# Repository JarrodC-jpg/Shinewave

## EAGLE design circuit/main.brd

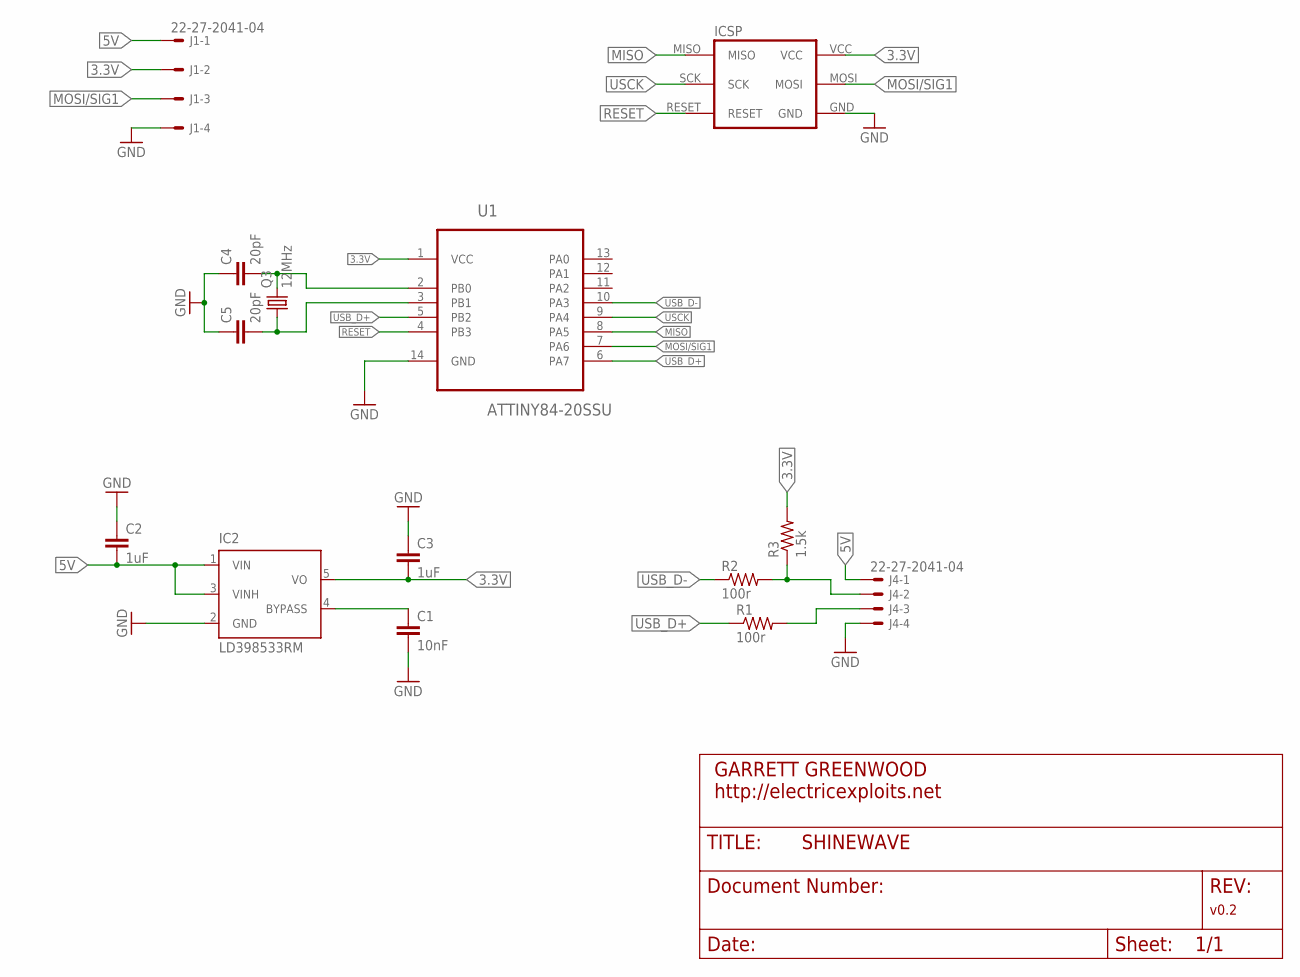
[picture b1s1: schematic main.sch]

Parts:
C1: 10nF; C0603
C2, C3: 1uF; C0603
C4, C5: 20pF; C0603
IC2: LD398533RM; SOT23-5L
J1, J4: 22-27-2041-04; 6410-04
Q3: 12MHz; CTS406
R1, R2: 100r; R0603
R3: 1.5k; R0603
U1: ATTINY84-20SSU; SOIC127P600X175-14N
U$1: ICSP_POGO_INTERFACE; ICSP_SMD

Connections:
3.3V: C3.2, IC2.5 (VO), J1.2, R3.2, U1.1 (VCC), U$1.VCC
5V: C2.2, IC2.1 (VIN), IC2.3 (VINH), J1.1, J4.1
GND: C1.2, C2.1, C3.1, C4.1, C5.1, IC2.2 (GND), J1.4, J4.4, U1.14 (GND), U$1.GND
MISO: U1.8 (PA5), U$1.MISO
MOSI/SIG1: J1.3, U1.7 (PA6), U$1.MOSI
unnamed: J4.2, R2.2, R3.1
unnamed: C1.1, IC2.4 (BYPASS)
unnamed: J4.3, R1.2
RESET: U1.4 (PB3), U$1.RESET
USB_D+: R1.1, U1.5 (PB2), U1.6 (PA7)
USB_D-: R2.1, U1.10 (PA3)
USCK: U1.9 (PA4), U$1.SCK
XTAL1: C4.2, Q3.3 (2), U1.2 (PB0)
XTAL2: C5.2, Q3.1, U1.3 (PB1)

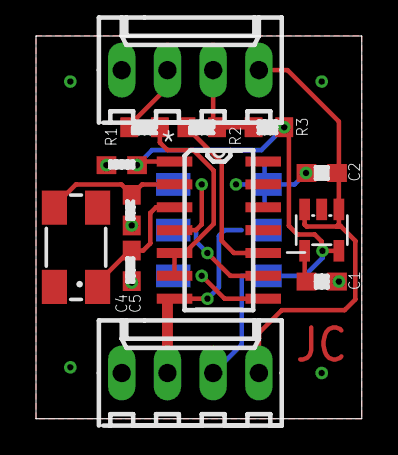
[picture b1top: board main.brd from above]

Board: 2 copper layers, 18.1 x 21.3 mm, 14 parts (0 on the bottom side), 14 nets.

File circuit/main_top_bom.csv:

Comment,Designator,Footprint,LCSC Part #
1.5k,R3,R0603,
1uF,C2 C3,C0603,
10nF,C1,C0603,
12MHz,Q3,CTS406,
20pF,C4 C5,C0603,
68,R1 R2,R0603,
ATTINY84-20SSU,U1,SOIC127P600X175-14N,
LD398533RM,IC2,SOT23-5L,

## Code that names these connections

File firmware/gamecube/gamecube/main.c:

#include <avr/interrupt.h>
#include <avr/wdt.h>
#include <stdint.h>
#include <util/delay.h>

#include "controller.h"
// #include "libs/Neopixel.h"
#include "usb.h"
#include "usbdrv/usbdrv.h"
#define DEBUG_MATCH 0   // Enable PIN_TIMER toggle on timer match
#define GCN_RETRY_LIMIT 5   // Number of times to retry the GCN signal line

#define PIN_DEBUG PA2
#define PIN_GC    PA6   // Needs to be connected to (DI)
//#define PIN_TIMER PA7   // Needs to be connected to (OC0B). Displays compare match toggles if DEBUG_MATCH is set

#define GET_BIT(TGT, PIN)    ((TGT) & (1 << (PIN)))
#define SET_BIT(TGT, PIN)    do { TGT |=  (1 << (PIN)); } while(0)
#define CLEAR_BIT(TGT, PIN)  do { TGT &= ~(1 << (PIN)); } while(0)
#define TOGGLE_BIT(TGT, PIN) do { TGT ^=  (1 << (PIN)); } while(0)

#define SEND_ZERO()        do { CLEAR_BIT(PORTA, PIN_GC); _delay_us(3); SET_BIT(PORTA, PIN_GC); _delay_us(1); } while(0)
#define SEND_ONE()         do { CLEAR_BIT(PORTA, PIN_GC); _delay_us(1); SET_BIT(PORTA, PIN_GC); _delay_us(3); } while(0)

void setup_pins(void) {
    CLEAR_BIT(DDRA, PIN_GC);		// Set PIN_GC as input, GCN data signal
    SET_BIT(PORTA, PIN_GC);		    // Enable pull-up resistor on PIN_GC
    SET_BIT(DDRA, PIN_DEBUG);       // Set PIN_DEBUG as output for debugging

    // Ensure that USB pins are inputs with pullup resistor disabled
    CLEAR_BIT(DDRB, PB2);
    CLEAR_BIT(DDRA, PA3);
    CLEAR_BIT(DDRA, PA7);
    CLEAR_BIT(PORTB, PB2);
    CLEAR_BIT(PORTA, PA3);
    CLEAR_BIT(PORTA, PA7);

    #if DEBUG_MATCH == 1
    SET_BIT(DDRA, PIN_TIMER);       // Set PIN_TIMER as output for compare matches
    #endif
}

void enable_timer0(void) {
    TCNT0 = 0;
    TIFR0 = 0xff;                   // Reset interrupt flags

    #if DEBUG_MATCH == 1
    // Set 0C0B(PA7) to toggle on match(COM0B=01)
    SET_BIT(TCCR0A, COM0B0);
    #endif

    // Enable Timer/Counter0 module at no prescaler
    SET_BIT(TCCR0B, CS00);
}

void disable_timer0(void) {
    #if DEBUG_MATCH == 1
    // Set 0C0B(PA7) to toggle on match(COM0B=01)
    CLEAR_BIT(TCCR0A, COM0B0);
    #endif

    // Disable Timer/Counter0 module
    CLEAR_BIT(TCCR0B, CS00);
}

// Set Timer/Counter0 in normal mode(WGM=000)
void setup_timer0(void) {
    disable_timer0();

    // Set compare match to signal critical point(2us)
    OCR0A = 2e-6 * F_CPU;   // Triggers USI clock source

    #if DEBUG_MATCH == 1
    OCR0B = 2e-6 * F_CPU;   // Triggers debug toggle
    #endif
}

void enable_usi(void) {
    // Enable Universal Serial Module in Two-wire mode(USIWM=10)
    SET_BIT(USICR, USIWM1);
}

void disable_usi(void) {
    // Disable Universal Serial Module
    SET_BIT(USICR, USIWM1);
}

void setup_usi(void) {
    // Set clock source to Timer/Counter0 Compare Match(USICS=01)
    SET_BIT(USICR, USICS0);
}

void setup_usb(void) {
    cli();
    wdt_enable(WDTO_1S);    // enable 1s watchdog timer
    usbInit();

    usbDeviceDisconnect();  // enforce re-enumeration
    uint8_t i;
    for(i = 0; i<250; i++) {
        wdt_reset();
        _delay_ms(2);
    }
    usbDeviceConnect();
    sei();
}

void init_controller(void) {
    SET_BIT(PORTA, PIN_GC);         // Set positive output on PIN_GC
    SET_BIT(DDRA, PIN_GC);          // Set PIN_GC as output

    // Send controller init message (000000001)
    for(uint8_t bit = 0; bit < 8; bit++) {
        SEND_ZERO();
    }
    SEND_ONE();

    CLEAR_BIT(DDRA, PIN_GC);        // Set PIN_GC as input
}

uint8_t request_message(uint8_t *message_buffer) {
    uint8_t cur_byte = 0;

    USISR = 0b11101000;             // Reset USI Interrupt flags and set timer value to 8
    disable_usi();
    disable_timer0();

    asm("nop; nop; nop;");

    SET_BIT(DDRA, PIN_GC);          // Set PIN_GC as output
    CLEAR_BIT(PORTA, PIN_GC);

    // Send controller data request
    SEND_ZERO(); SEND_ONE();  SEND_ZERO(); SEND_ZERO(); SEND_ZERO(); SEND_ZERO(); SEND_ZERO(); SEND_ZERO();
    SEND_ZERO(); SEND_ZERO(); SEND_ZERO(); SEND_ZERO(); SEND_ZERO(); SEND_ZERO(); SEND_ONE();  SEND_ONE();
    SEND_ZERO(); SEND_ZERO(); SEND_ZERO(); SEND_ZERO(); SEND_ZERO(); SEND_ZERO(); SEND_ONE();  SEND_ZERO();
    SEND_ZERO();

    SET_BIT(PORTA, PIN_GC);
    CLEAR_BIT(DDRA, PIN_GC);        // Set PIN_GC as input

    // Start reading the message
    enable_usi();
    enable_timer0();
    while(1) {
	
        // Wait for signal to go low
        while(GET_BIT(PINA, PIN_GC)) {
            // Catch a timer overflow as an exit condition
            // This occurs if the signal is high for > 255 cycles
            if(GET_BIT(TIFR0, TOV0)) {
                // Exit condition
                disable_usi();

                // Wait for the timer to overflow and loop once, fixes 'every other' corruption
                while(TCNT0 < 24) {}

                // Check if there's no signal on the line
                if(cur_byte == 0) {
                    SET_BIT(PORTA, PIN_DEBUG);
                    CLEAR_BIT(PORTA, PIN_DEBUG);
                    return 0;
                }

                disable_timer0();
                return 1;
            }
        }
        // Reset Timer0, a little higher than 0 to account for polling delay
        TCNT0 = 5;

        if(GET_BIT(USISR, USIOIF)) {
            // Skip the counter to 8 of 16
            SET_BIT(USISR, USICNT3);

            // Store the byte from the serial buffer
            message_buffer[cur_byte] = USIBR;
            cur_byte++;

            // Toggle the debug pin
            SET_BIT(PORTA, PIN_DEBUG);
            CLEAR_BIT(PORTA, PIN_DEBUG);

            // Clear the overflow counter
            SET_BIT(USISR, USIOIF);
        }

        // Make sure signal is high before looping
        // Hardware should pull up DIN or risk an infinite loop
        while(!GET_BIT(PINA, PIN_GC)) {}
    }

    // Unreachable code
    return 0;
}

int main(void)
{
    setup_pins();
    setup_timer0();
    setup_usi();
    setup_usb();
    init_controller();

    uint8_t retry_count = 0;

    uint8_t message_buffer[8] = {0};
    Controller *controller = (Controller*)message_buffer;

    while(1) {
        usbPoll();
        wdt_reset();

        if(usbInterruptIsReady()) {
            // Zero out input array
            for(uint8_t i = 0; i < 8; ++i) {
                message_buffer[i] = 0xf0;
            }
            // Try to grab the controller state
            retry_count = GCN_RETRY_LIMIT;
            while(retry_count--) {
                if(request_message(message_buffer)) {
                    build_report(controller, &reportBuffer);
                    usbSetInterrupt((void *)&reportBuffer, sizeof(reportBuffer));
                    if(reportBuffer.rx == 255) {
                        _delay_us(1);
                    }
                    break;
                }

            }
        }
    }
}

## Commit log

2021-06-23 my own board
